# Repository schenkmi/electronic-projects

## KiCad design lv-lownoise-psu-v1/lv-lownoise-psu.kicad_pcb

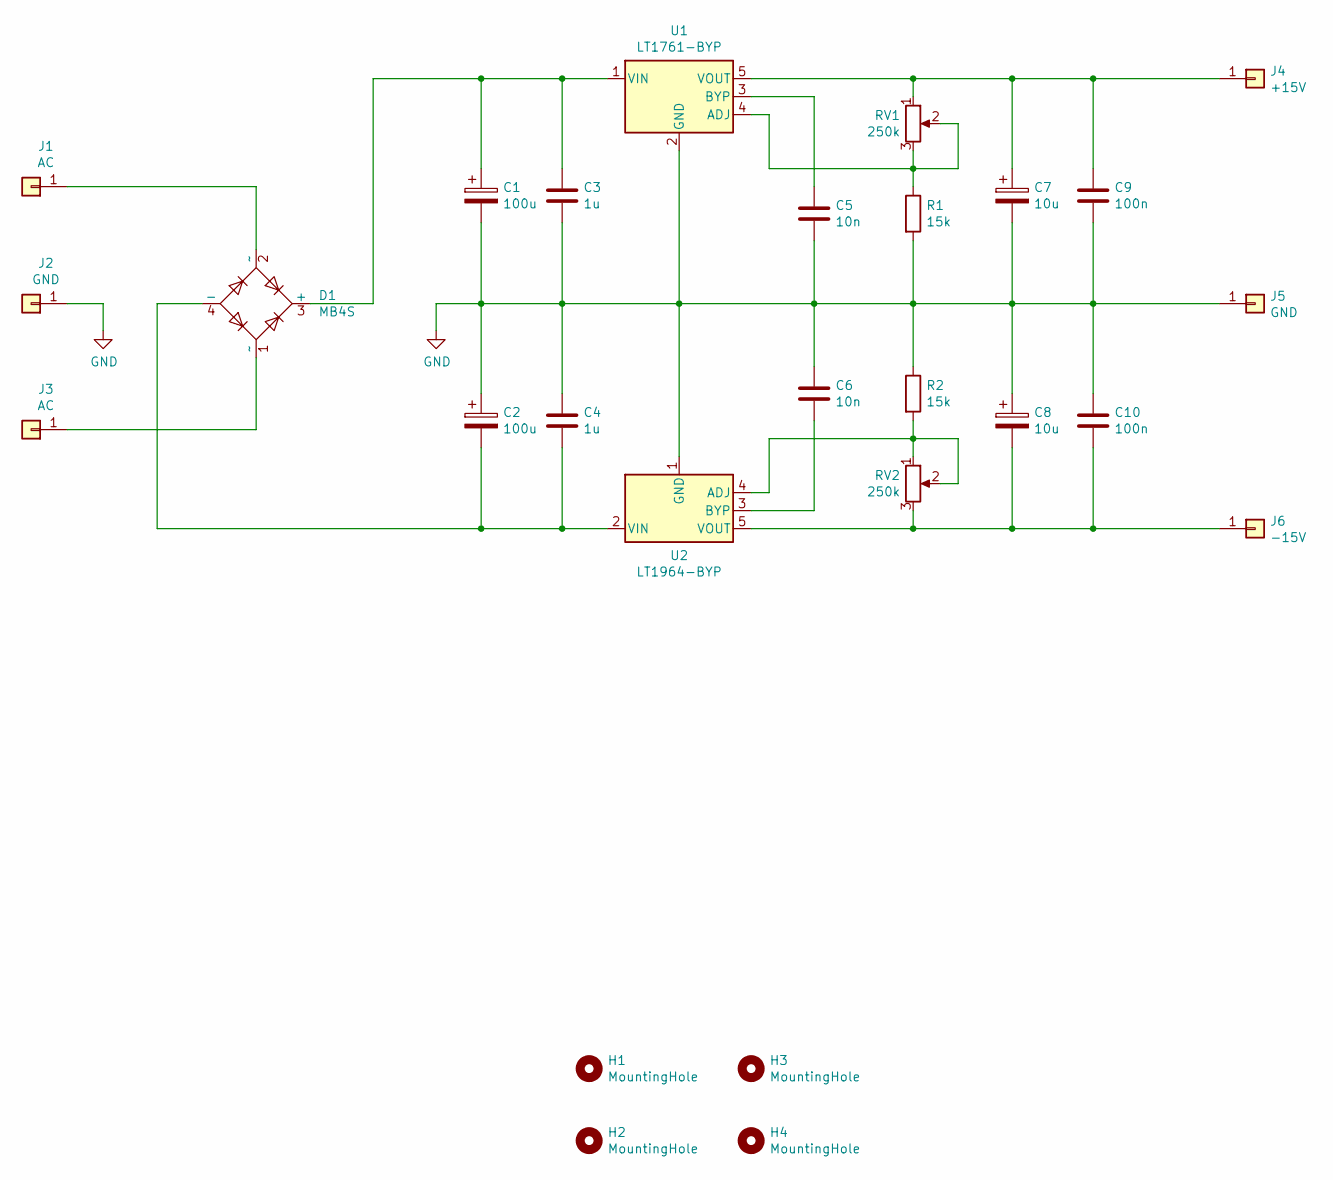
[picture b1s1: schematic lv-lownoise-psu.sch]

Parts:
C1, C2: 100u; CP_Elec_8x10
C3, C4: 1u; C_0805_2012Metric_Pad1.18x1.45mm_HandSolder
C5, C6: 10n; C_0805_2012Metric_Pad1.18x1.45mm_HandSolder
C7, C8: 10u; CP_EIA-3528-12_Kemet-T_Pad1.50x2.35mm_HandSolder
C9, C10: 100n; C_0805_2012Metric_Pad1.18x1.45mm_HandSolder
D1: MB4S; TO-269AA
H1, H2, H3, H4: MountingHole; MountingHole_3.2mm_M3
J1, J3: AC; Pin_D1.3mm_L11.0mm
J2, J5: GND; Pin_D1.3mm_L11.0mm
J4: +15V; Pin_D1.3mm_L11.0mm
J6: -15V; Pin_D1.3mm_L11.0mm
R1, R2: 15k; R_0805_2012Metric_Pad1.20x1.40mm_HandSolder
RV1, RV2: 250k; Potentiometer_Bourns_3296W_Vertical
U1: LT1761-BYP; TSOT-23-5
U2: LT1964-BYP; TSOT-23-5

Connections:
GND: C1.2, C2.1, C3.2, C4.1, C5.2, C6.1, C7.2, C8.1, C9.2, C10.1, J2.1, J5.1, R1.2, R2.1, U1.2 (GND), U2.1 (GND)
unnamed: C1.1, C3.1, D1.3 (+), U1.1 (VIN)
unnamed: C2.2, C4.2, D1.4 (-), U2.2 (VIN)
unnamed: C5.1, U1.3 (BYP)
unnamed: C6.2, U2.3 (BYP)
unnamed: C7.1, C9.1, J4.1, RV1.1, U1.5 (VOUT)
unnamed: C8.2, C10.2, J6.1, RV2.3, U2.5 (VOUT)
unnamed: D1.1 (~~), J3.1
unnamed: D1.2 (~~), J1.1
unnamed: R1.1, RV1.2, RV1.3, U1.4 (ADJ)
unnamed: R2.2, RV2.1, RV2.2, U2.4 (ADJ)

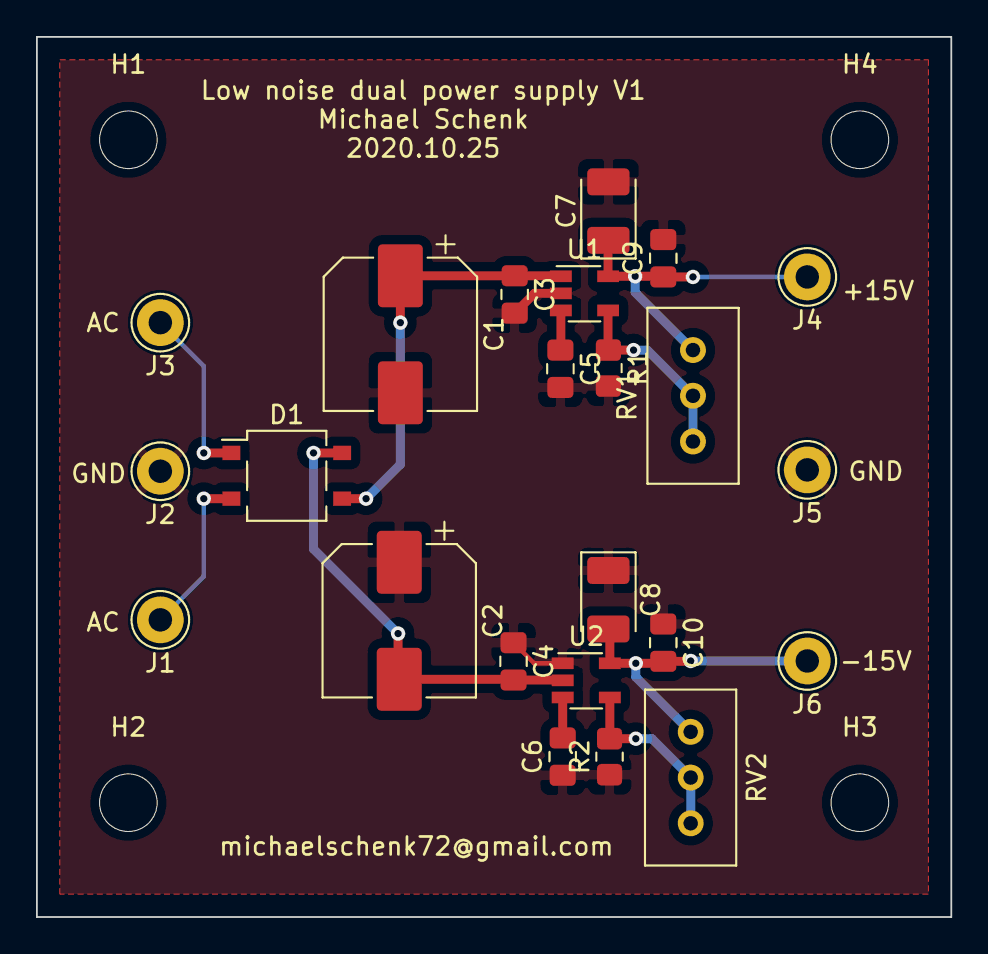
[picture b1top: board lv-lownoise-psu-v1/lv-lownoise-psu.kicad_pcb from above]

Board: 2 copper layers, 50.8 x 48.9 mm, 27 parts (0 on the bottom side), 11 nets.

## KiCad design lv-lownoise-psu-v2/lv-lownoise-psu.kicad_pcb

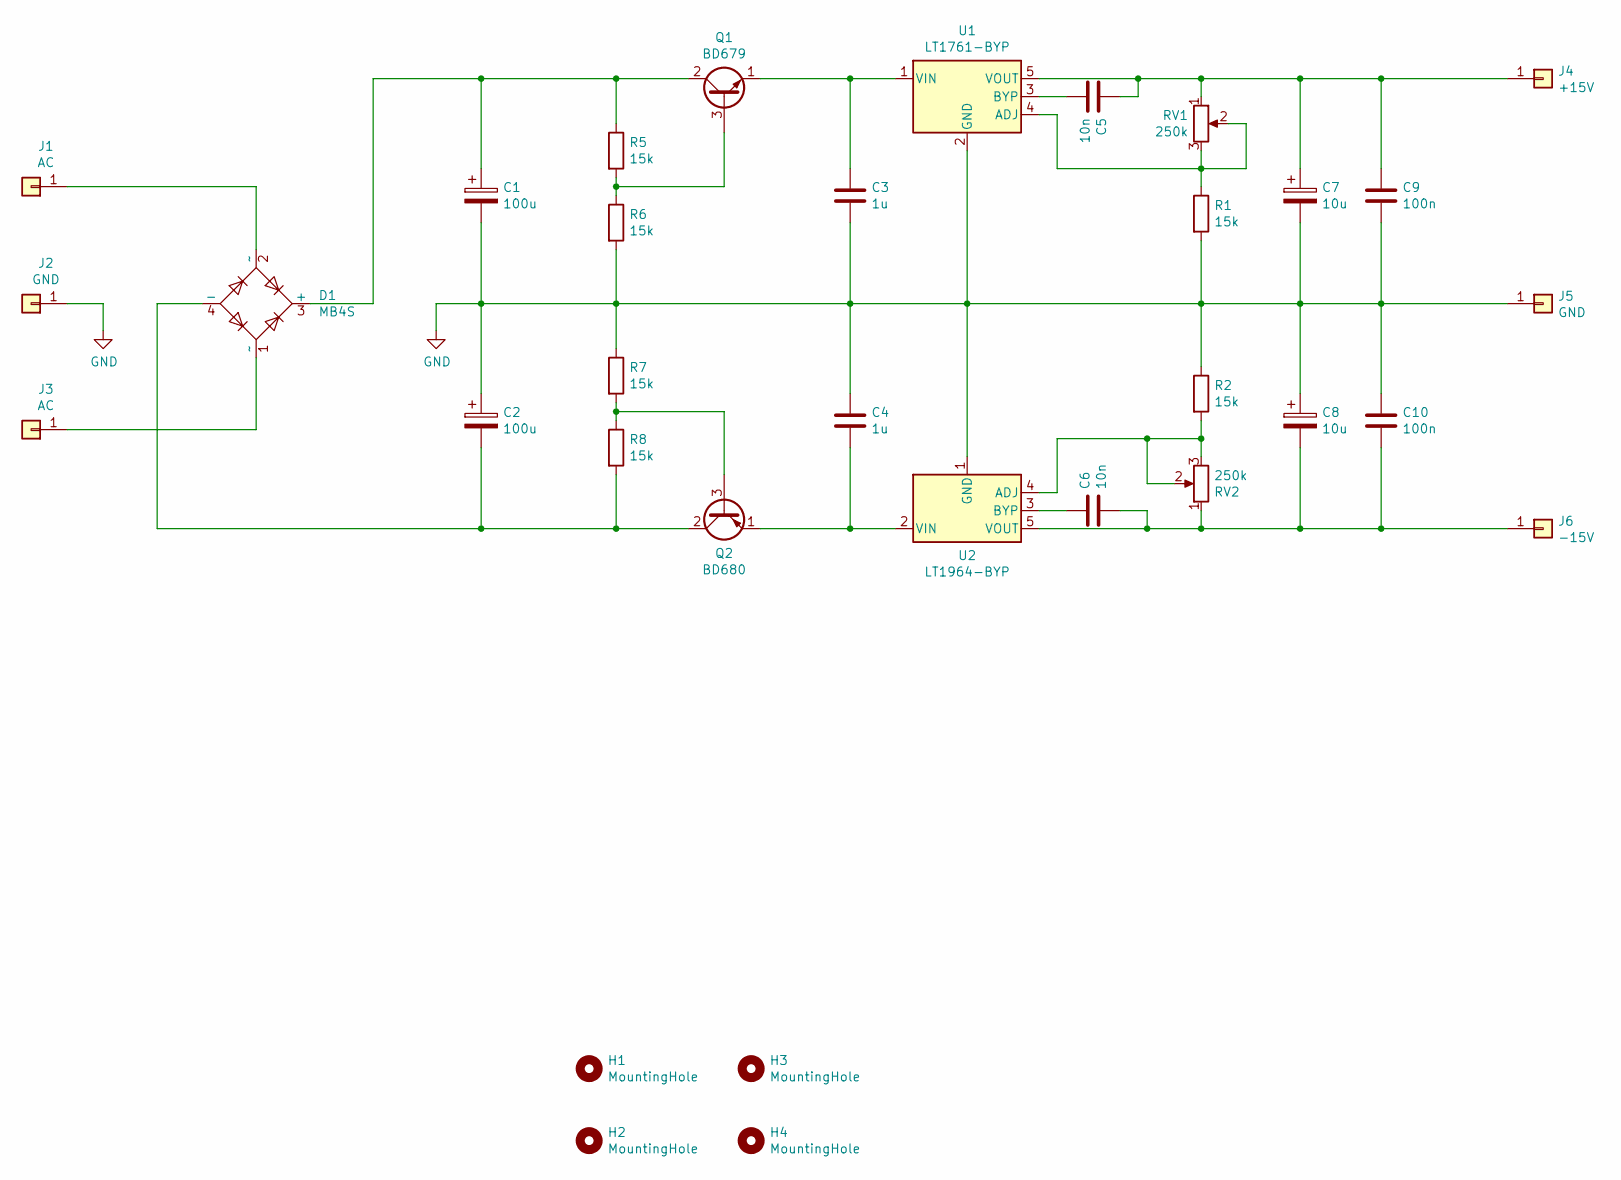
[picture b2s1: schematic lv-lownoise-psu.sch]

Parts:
C1, C2: 100u; CP_Elec_8x10
C3, C4: 1u; C_0805_2012Metric_Pad1.18x1.45mm_HandSolder
C5, C6: 10n; C_0805_2012Metric_Pad1.18x1.45mm_HandSolder
C7, C8: 10u; CP_EIA-3528-12_Kemet-T_Pad1.50x2.35mm_HandSolder
C9, C10: 100n; C_0805_2012Metric_Pad1.18x1.45mm_HandSolder
D1: MB4S; TO-269AA
H1, H2, H3, H4: MountingHole; MountingHole_3.2mm_M3
J1, J3: AC; Pin_D1.3mm_L11.0mm
J2, J5: GND; Pin_D1.3mm_L11.0mm
J4: +15V; Pin_D1.3mm_L11.0mm
J6: -15V; Pin_D1.3mm_L11.0mm
Q1: BD679; TO-126-3_Vertical
Q2: BD680; TO-126-3_Vertical
R1, R2, R5, R6, R7, R8: 15k; R_0805_2012Metric_Pad1.20x1.40mm_HandSolder
RV1, RV2: 250k; Potentiometer_Bourns_3296W_Vertical
U1: LT1761-BYP; TSOT-23-5
U2: LT1964-BYP; TSOT-23-5

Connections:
GND: C1.2, C2.1, C3.2, C4.1, C7.2, C8.1, C9.2, C10.1, J2.1, J5.1, R1.2, R2.1, R6.2, R7.1, U1.2 (GND), U2.1 (GND)
unnamed: C1.1, D1.3 (+), Q1.2 (C), R5.1
unnamed: C2.2, D1.4 (-), Q2.2 (C), R8.2
unnamed: C3.1, Q1.1 (E), U1.1 (VIN)
unnamed: C4.2, Q2.1 (E), U2.2 (VIN)
unnamed: C5.1, C7.1, C9.1, J4.1, RV1.1, U1.5 (VOUT)
unnamed: C5.2, U1.3 (BYP)
unnamed: C6.1, U2.3 (BYP)
unnamed: C6.2, C8.2, C10.2, J6.1, RV2.1, U2.5 (VOUT)
unnamed: D1.1 (~~), J3.1
unnamed: D1.2 (~~), J1.1
unnamed: Q1.3 (B), R5.2, R6.1
unnamed: Q2.3 (B), R7.2, R8.1
unnamed: R1.1, RV1.2, RV1.3, U1.4 (ADJ)
unnamed: R2.2, RV2.2, RV2.3, U2.4 (ADJ)

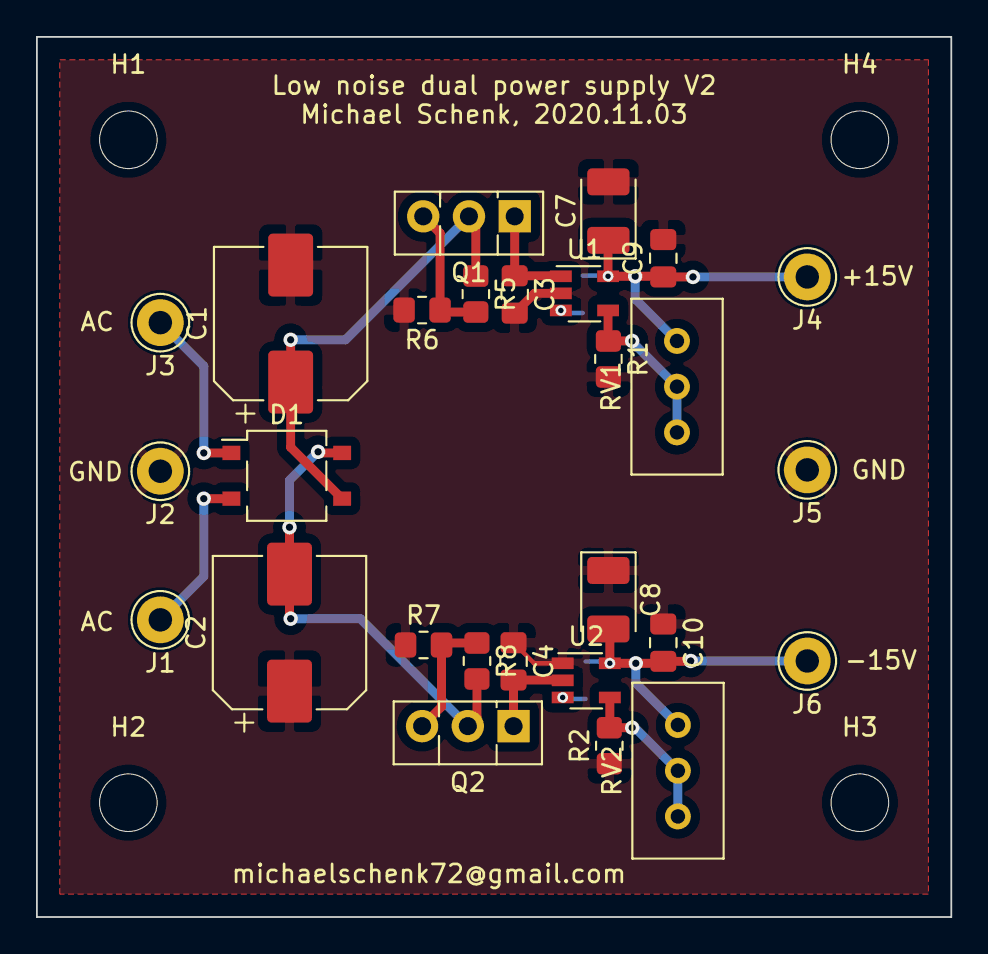
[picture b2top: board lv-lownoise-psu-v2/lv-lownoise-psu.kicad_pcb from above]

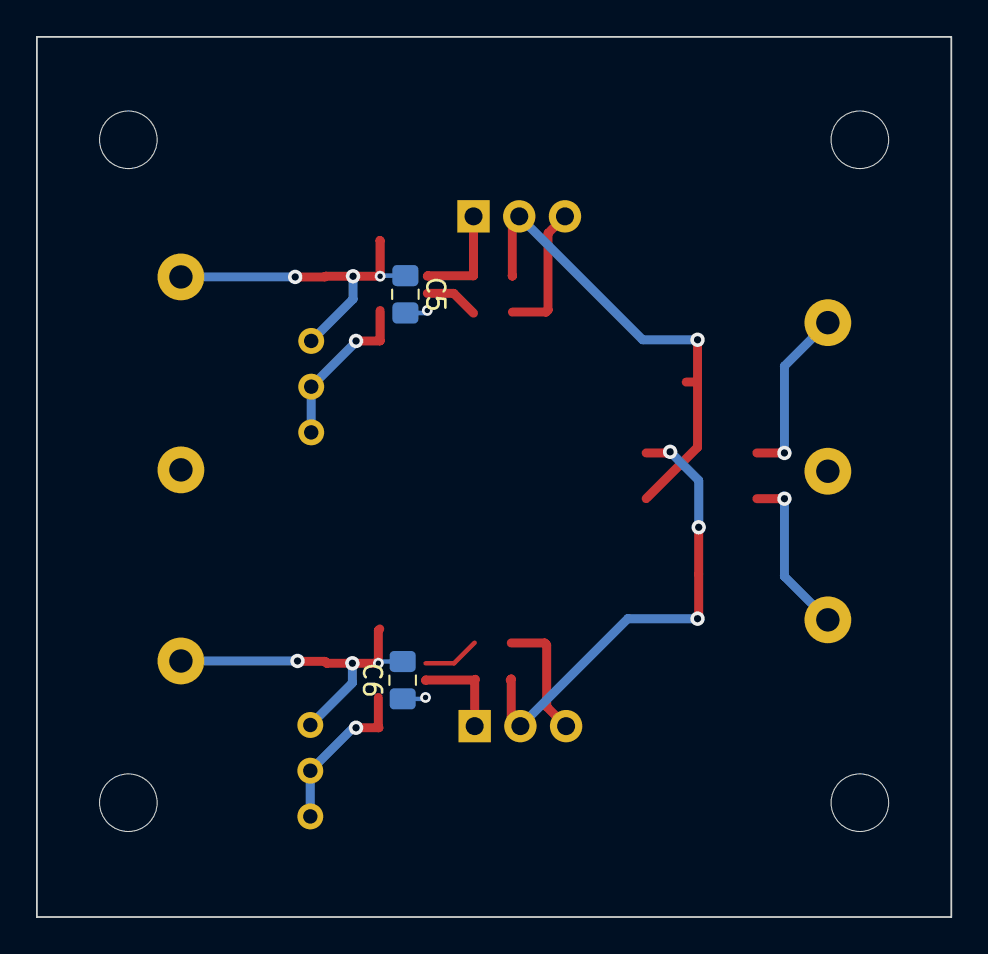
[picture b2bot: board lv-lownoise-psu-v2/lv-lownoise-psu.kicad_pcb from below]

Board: 2 copper layers, 50.8 x 48.9 mm, 33 parts (2 on the bottom side), 15 nets.
